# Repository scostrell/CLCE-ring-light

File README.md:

# CLCE Ring Light

Provision new board [as Pico](https://circuitpython.org/board/raspberry_pi_pico/)
- The GPIO25 LED matches the Pico's, and should show status

Deploy code:
```sh
./deploy.sh
```

Main components
STP16CPC26P

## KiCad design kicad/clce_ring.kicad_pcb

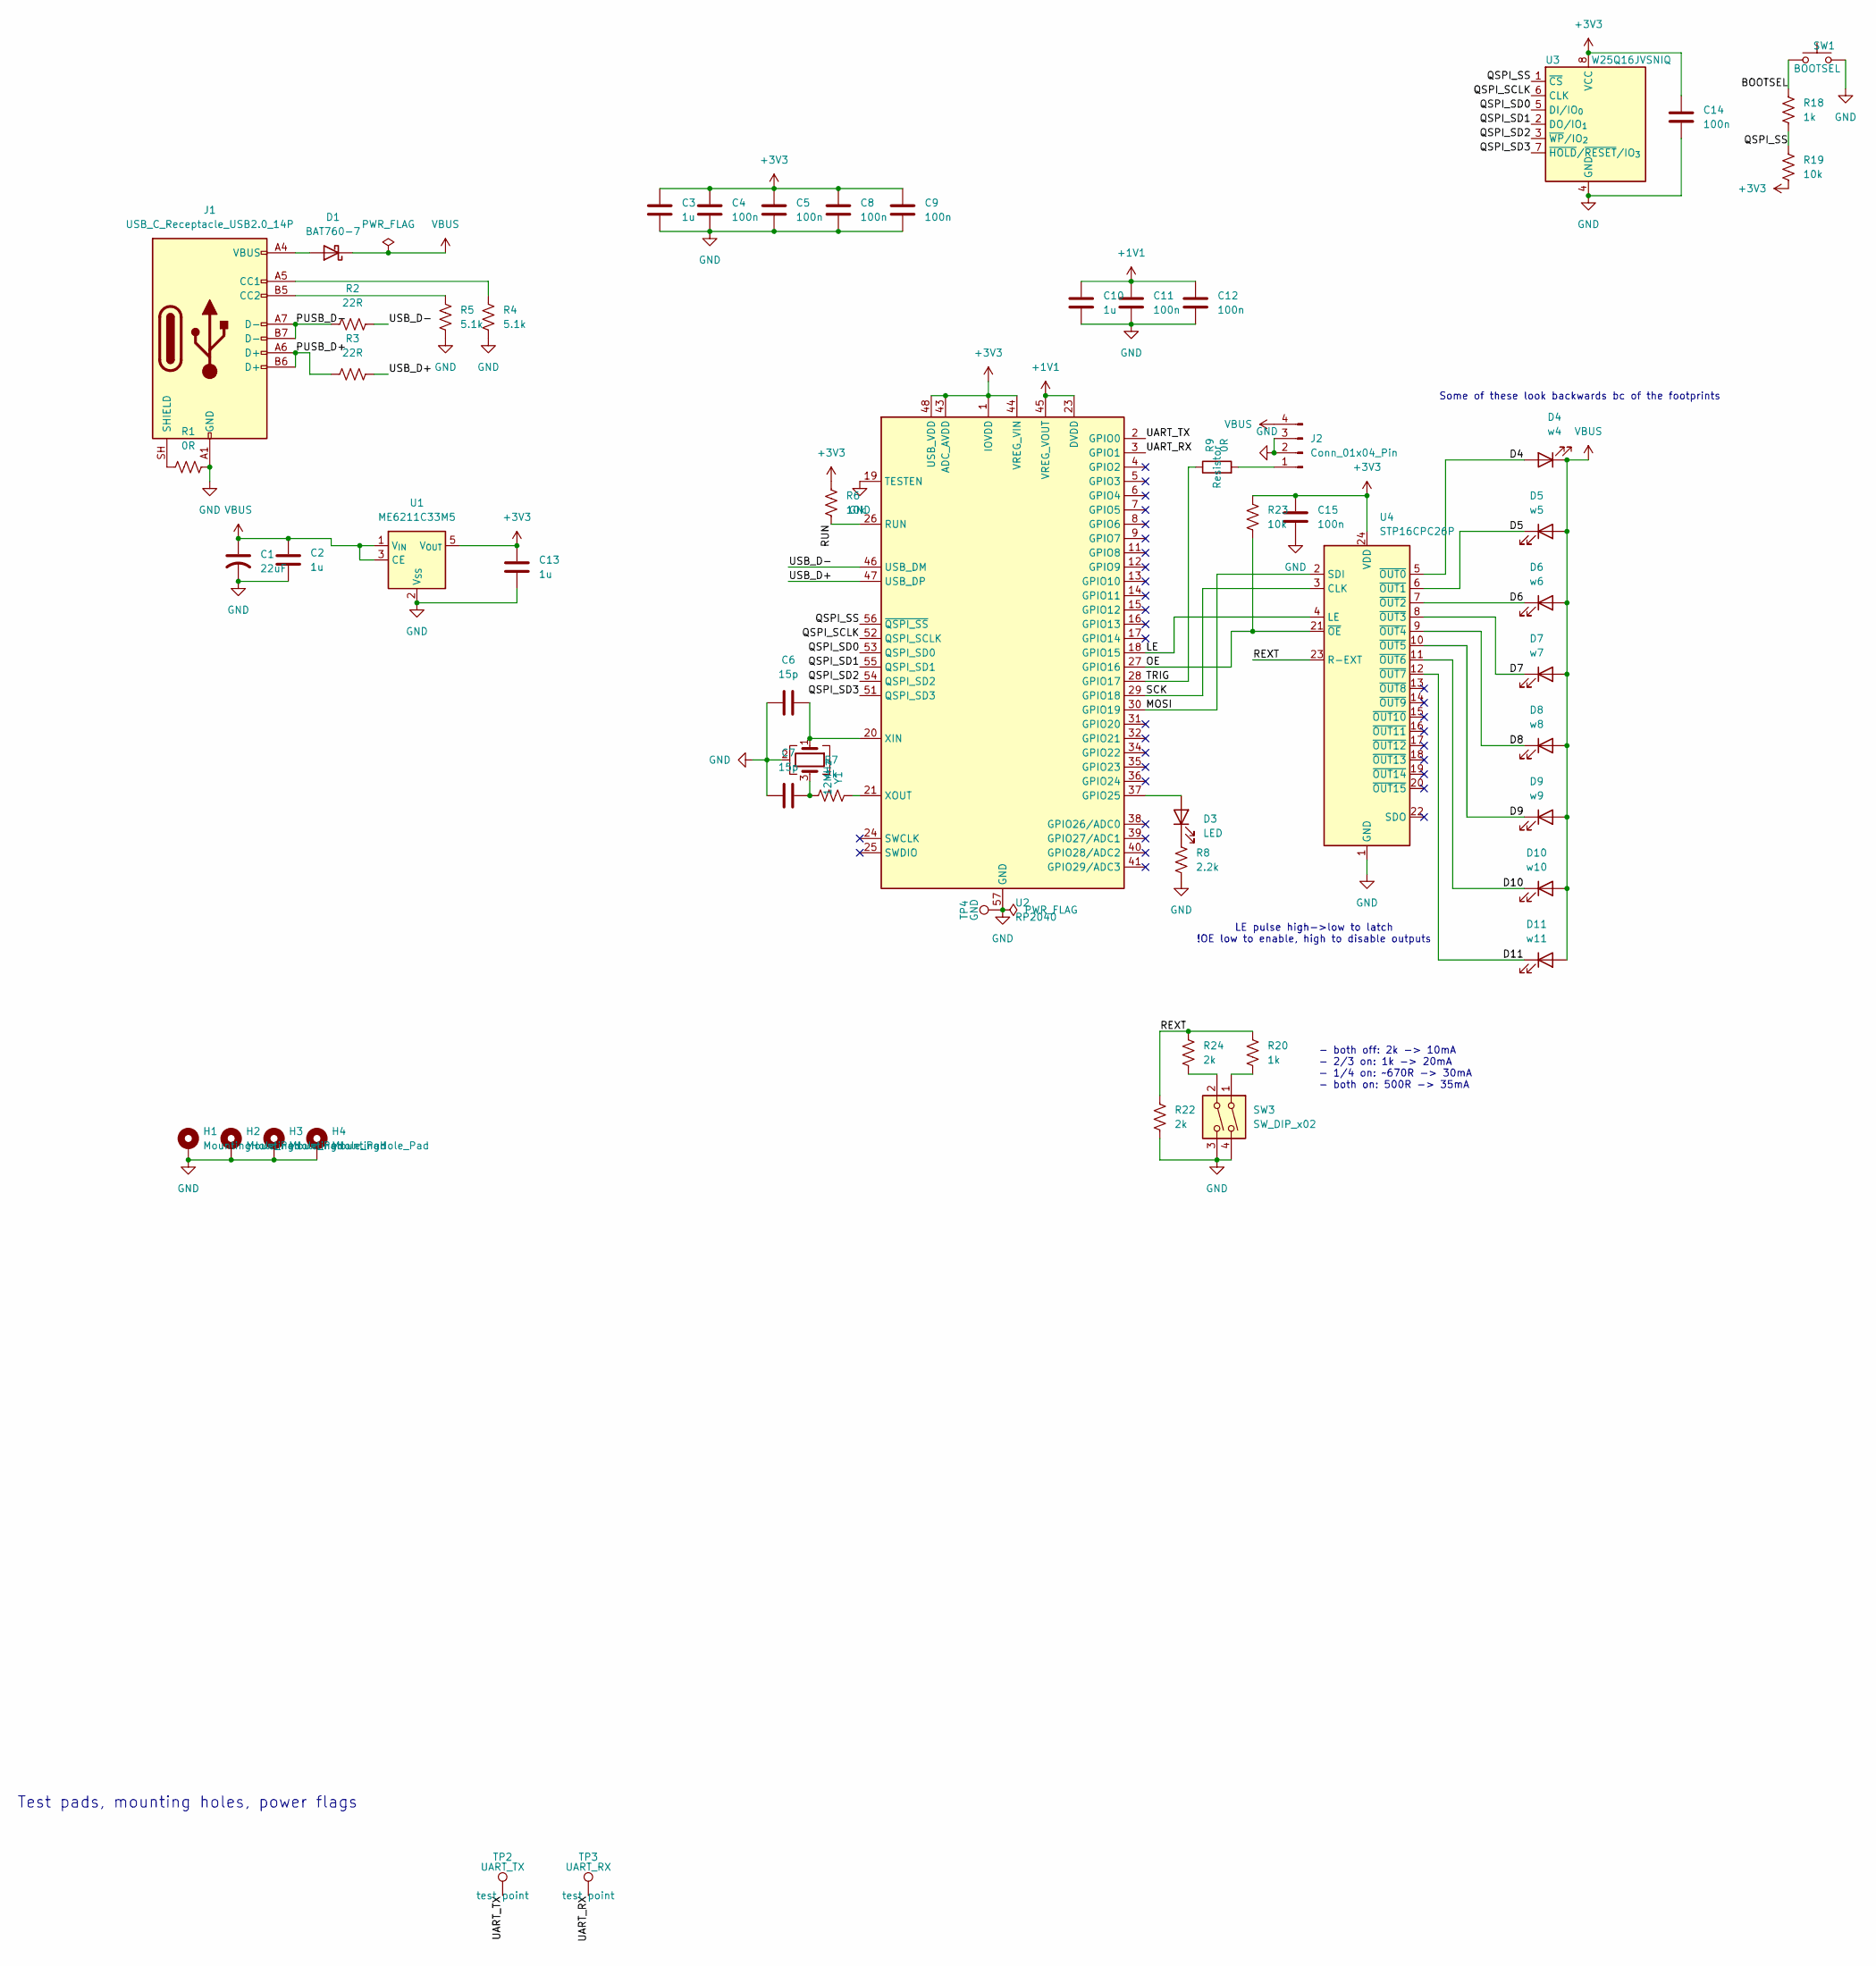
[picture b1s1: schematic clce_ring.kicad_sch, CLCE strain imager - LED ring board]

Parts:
C1: 22uF; C_0603_1608Metric; LCSC C45783
C2, C3, C10, C13: 1u; C_0603_1608Metric; LCSC C15849
C4, C5, C8, C9, C11, C12, C14, C15: 100n; C_0402_1005Metric; LCSC C1525
C6, C7: 15p; C_0402_1005Metric; LCSC C1548
D1: BAT760-7; D_SOD-323; LCSC C124187
D3: LED; LED_0603_1608Metric; LCSC C2286
D4: w4; LED_Everlight-SMD3528_3.5x2.8mm_67-21ST; LCSC C22466158
D5: w5; LED_Everlight-SMD3528_3.5x2.8mm_67-21ST; LCSC C440444
D6: w6; LED_Everlight-SMD3528_3.5x2.8mm_67-21ST; LCSC C440443
D7: w7; LED_Everlight-SMD3528_3.5x2.8mm_67-21ST; LCSC C5280496
D8: w8; LED_Everlight-SMD3528_3.5x2.8mm_67-21ST; LCSC C440442
D9: w9; LED_Everlight-SMD3528_3.5x2.8mm_67-21ST; LCSC C440441
D10: w10; LED_Everlight-SMD3528_3.5x2.8mm_67-21ST; LCSC C22447954
D11: w11; LED_Everlight-SMD3528_3.5x2.8mm_67-21ST; LCSC C17485563
H1, H2, H3, H4: MountingHole_Pad; MountingHole_2.1mm
J1: USB_C_Receptacle_USB2.0_14P; USB_C_Receptacle_GCT_USB4105-xx-A_16P_TopMnt_Horizontal; LCSC C3020560
J2: Conn_01x04_Pin; PinHeader_1x04_P2.54mm_Vertical
R1, R9: 0R; R_0402_1005Metric; LCSC C17168
R2, R3: 22R; R_0402_1005Metric; LCSC C25092
R4, R5: 5.1k; R_0402_1005Metric; LCSC C25905
R6, R19, R23: 10k; R_0402_1005Metric; LCSC C25744
R7, R18, R20: 1k; R_0402_1005Metric; LCSC C11702
R8: 2.2k; R_0402_1005Metric; LCSC C25879
R22, R24: 2k; R_0402_1005Metric; LCSC C4109
SW1: BOOTSEL; SW_SPST_B3U-1000P; MPN Omron B3U-1000P; LCSC C231329
SW3: SW_DIP_x02; SW_DIP_SPSTx02_Slide_KingTek_DSHP02TS_W7.62mm_P1.27mm; LCSC C319052
TP2: UART_TX; TestPoint_Pad_D1.0mm
TP3: UART_RX; TestPoint_Pad_D1.0mm
TP4: GND; TestPoint_Pad_D1.0mm
U1: ME6211C33M5; SOT-23-5; LCSC C82942
U2: RP2040; QFN-56-1EP_7x7mm_P0.4mm_EP3.2x3.2mm; LCSC C2040
U3: W25Q16JVSNIQ; SOIC-8_3.9x4.9mm_P1.27mm; MPN Winbond W25Q16JVSNIQ; LCSC C2456211
U4: STP16CPC26P; QSOP-24_3.9x8.7mm_P0.635mm; LCSC C2678802
Y1: 12MHz; Crystal_SMD_3225-4Pin_3.2x2.5mm; MPN Abracon ABM8-272-T3; LCSC C20625731

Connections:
+1V1: C10.1, C11.1, C12.1, U2.23 (DVDD), U2.45 (VREG_VOUT), U2.50 (DVDD)
+3V3: C3.1, C4.1, C5.1, C8.1, C9.1, C13.1, C14.1, C15.1, R6.2, R19.1, R23.2, U1.5 (V_{OUT}), U2.1 (IOVDD), U2.10 (IOVDD), U2.22 (IOVDD), U2.33 (IOVDD), U2.42 (IOVDD), U2.43 (ADC_AVDD), U2.44 (VREG_VIN), U2.48 (USB_VDD), U2.49 (IOVDD), U3.8 (VCC), U4.24 (VDD)
/BOOTSEL: R18.2, SW1.1
/D4: D4.2 (A), U4.5 (~OUT0)
/D5: D5.1 (K), U4.6 (~OUT1)
/D6: D6.1 (K), U4.7 (~OUT2)
/D7: D7.1 (K), U4.8 (~OUT3)
/D8: D8.1 (K), U4.9 (~OUT4)
/D9: D9.1 (K), U4.10 (~OUT5)
/D10: D10.1 (K), U4.11 (~OUT6)
/D11: D11.1 (K), U4.12 (~OUT7)
/LE: U2.18 (GPIO15), U4.4 (LE)
/MOSI: U2.30 (GPIO19), U4.2 (SDI)
/OE: R23.1, U2.27 (GPIO16), U4.21 (~OE)
/PUSB_D+: J1.A6 (D+), J1.B6 (D+), R3.1
/PUSB_D-: J1.A7 (D-), J1.B7 (D-), R2.1
/QSPI_SCLK: U2.52 (QSPI_SCLK), U3.6 (CLK)
/QSPI_SD0: U2.53 (QSPI_SD0), U3.5 (DI/IO_{0})
/QSPI_SD1: U2.55 (QSPI_SD1), U3.2 (DO/IO_{1})
/QSPI_SD2: U2.54 (QSPI_SD2), U3.3 (~WP/IO_{2})
/QSPI_SD3: U2.51 (QSPI_SD3), U3.7 (~HOLD/~RESET/IO_{3})
/QSPI_SS: R18.1, R19.2, U2.56 (~QSPI_SS), U3.1 (~CS)
/REXT: R20.2, R22.2, R24.2, U4.23 (R-EXT)
/RUN: R6.1, U2.26 (RUN)
/SCK: U2.29 (GPIO18), U4.3 (CLK)
/TRIG: R9.1, U2.28 (GPIO17)
/UART_RX: TP3.1 (1_1), U2.3 (GPIO1)
/UART_TX: TP2.1 (1_1), U2.2 (GPIO0)
/USB_D+: R3.2, U2.47 (USB_DP)
/USB_D-: R2.2, U2.46 (USB_DM)
GND: C1.2, C2.2, C3.2, C4.2, C5.2, C6.1, C7.1, C8.2, C9.2, C10.2, C11.2, C12.2, C13.2, C14.2, C15.2, H1.1, H2.1, H3.1, H4.1, J1.A1 (GND), J1.A12 (GND), J1.B1 (GND), J1.B12 (GND), J2.2, J2.3, R1.2, R4.2, R5.2, R8.1, R22.1, SW1.2, SW3.3, SW3.4, TP4.1 (1_1), U1.2 (V_{SS}), U2.19 (TESTEN), U2.57 (GND), U3.4 (GND), U4.1 (GND), Y1.2 (G), Y1.4 (G)
unnamed: C7.2, R7.1, Y1.3
unnamed: D1.2 (A), J1.A4 (VBUS), J1.A9 (VBUS), J1.B4 (VBUS), J1.B9 (VBUS)
unnamed: D3.2 (A), U2.37 (GPIO25)
unnamed: D3.1 (K), R8.2
unnamed: J1.A5 (CC1), R4.1
unnamed: J1.B5 (CC2), R5.1
unnamed: J1.SH (SHIELD), R1.1
unnamed: J2.1, R9.2
unnamed: R20.1, SW3.1
unnamed: R24.1, SW3.2
unnamed: C6.2, U2.20 (XIN), Y1.1
unnamed: R7.2, U2.21 (XOUT)
VBUS: C1.1, C2.1, D1.1 (K), D4.1 (K), D5.2 (A), D6.2 (A), D7.2 (A), D8.2 (A), D9.2 (A), D10.2 (A), D11.2 (A), J2.4, U1.1 (V_{IN}), U1.3 (CE)

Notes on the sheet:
LE pulse high->low to latch !OE low to enable, high to disable outputs
- both off: 2k -> 10mA - 2/3 on: 1k -> 20mA - 1/4 on: ~670R -> 30mA - both on: 500R -> 35mA
Test pads, mounting holes, power flags
Some of these look backwards bc of the footprints

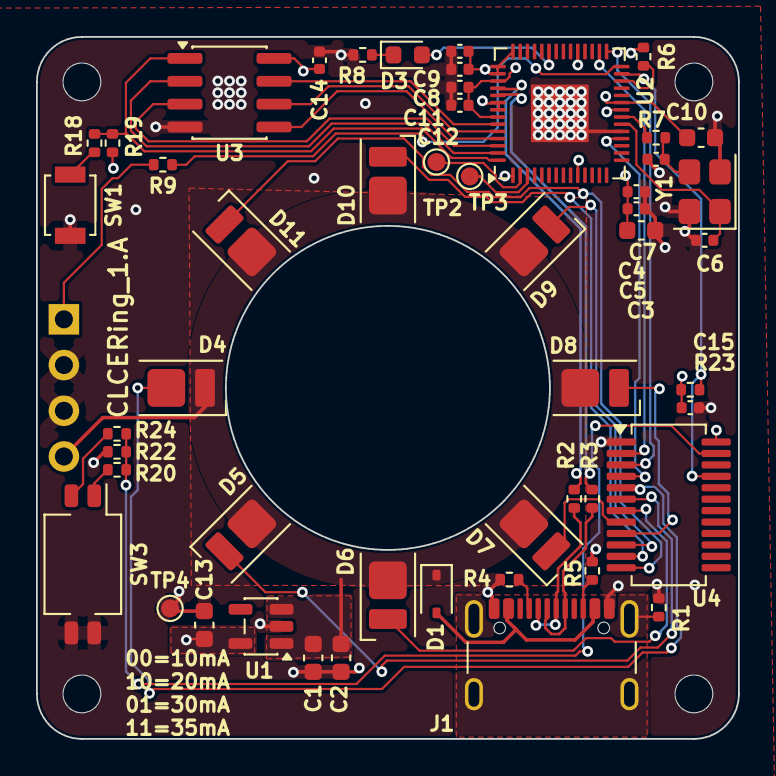
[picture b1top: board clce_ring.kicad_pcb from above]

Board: 4 copper layers, 39.0 x 39.0 mm, 56 parts (1 on the bottom side), 44 nets.
